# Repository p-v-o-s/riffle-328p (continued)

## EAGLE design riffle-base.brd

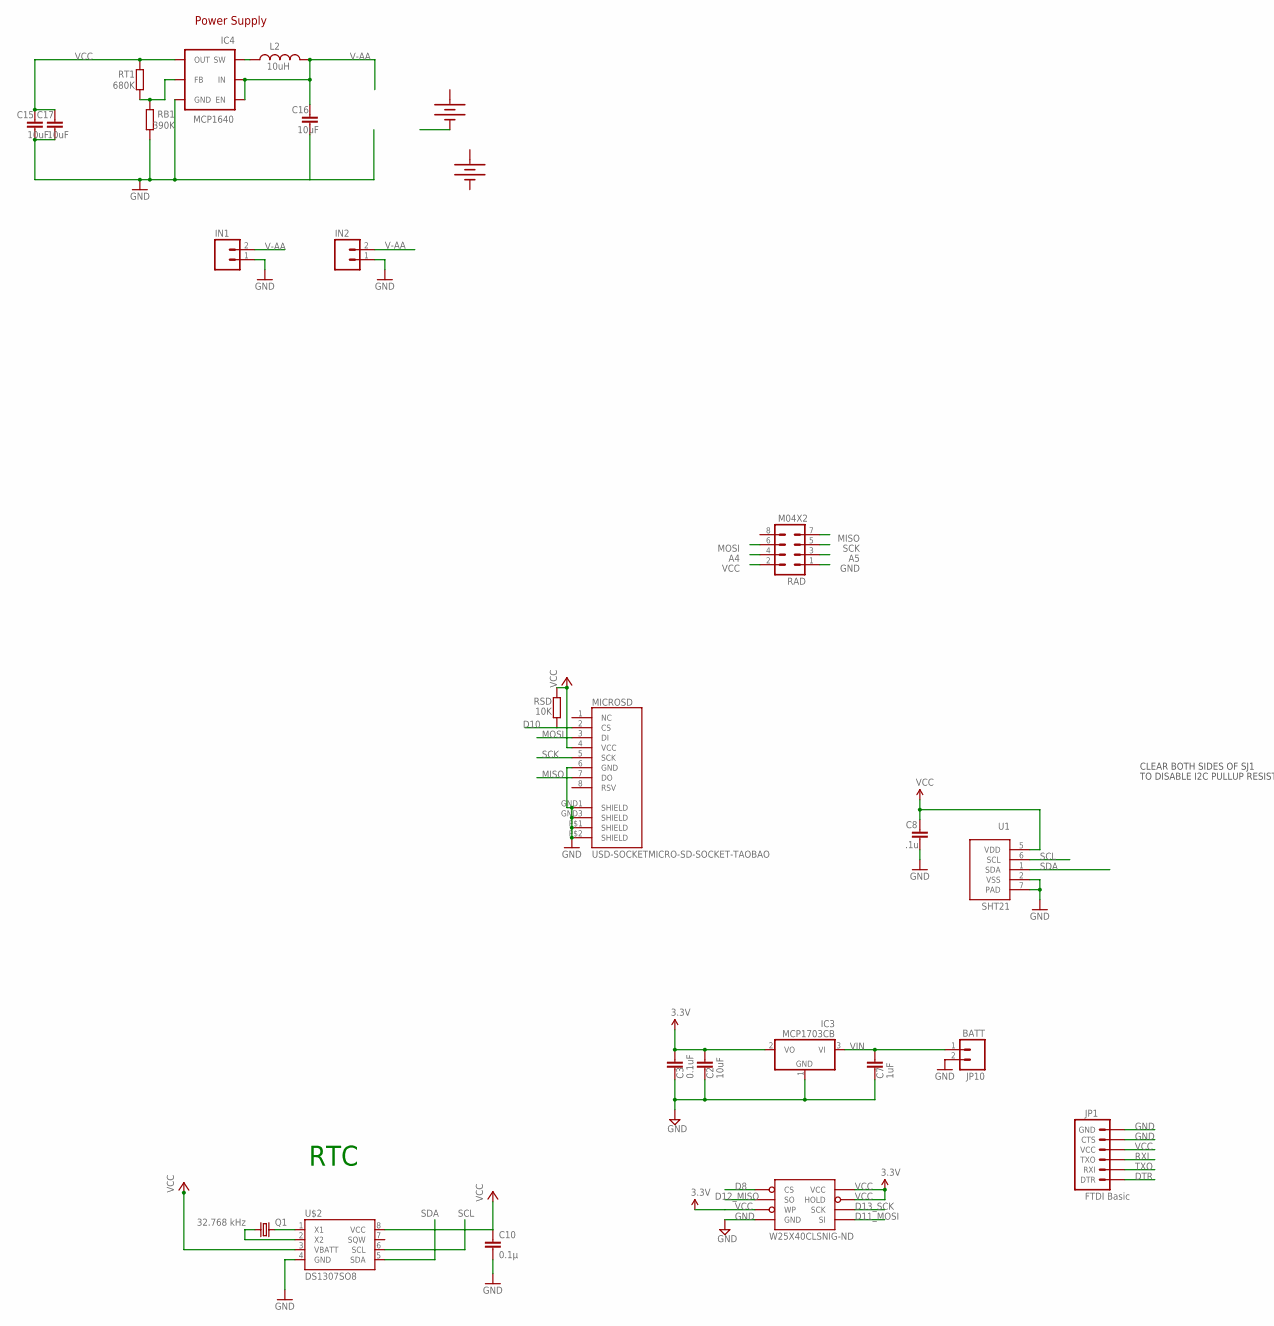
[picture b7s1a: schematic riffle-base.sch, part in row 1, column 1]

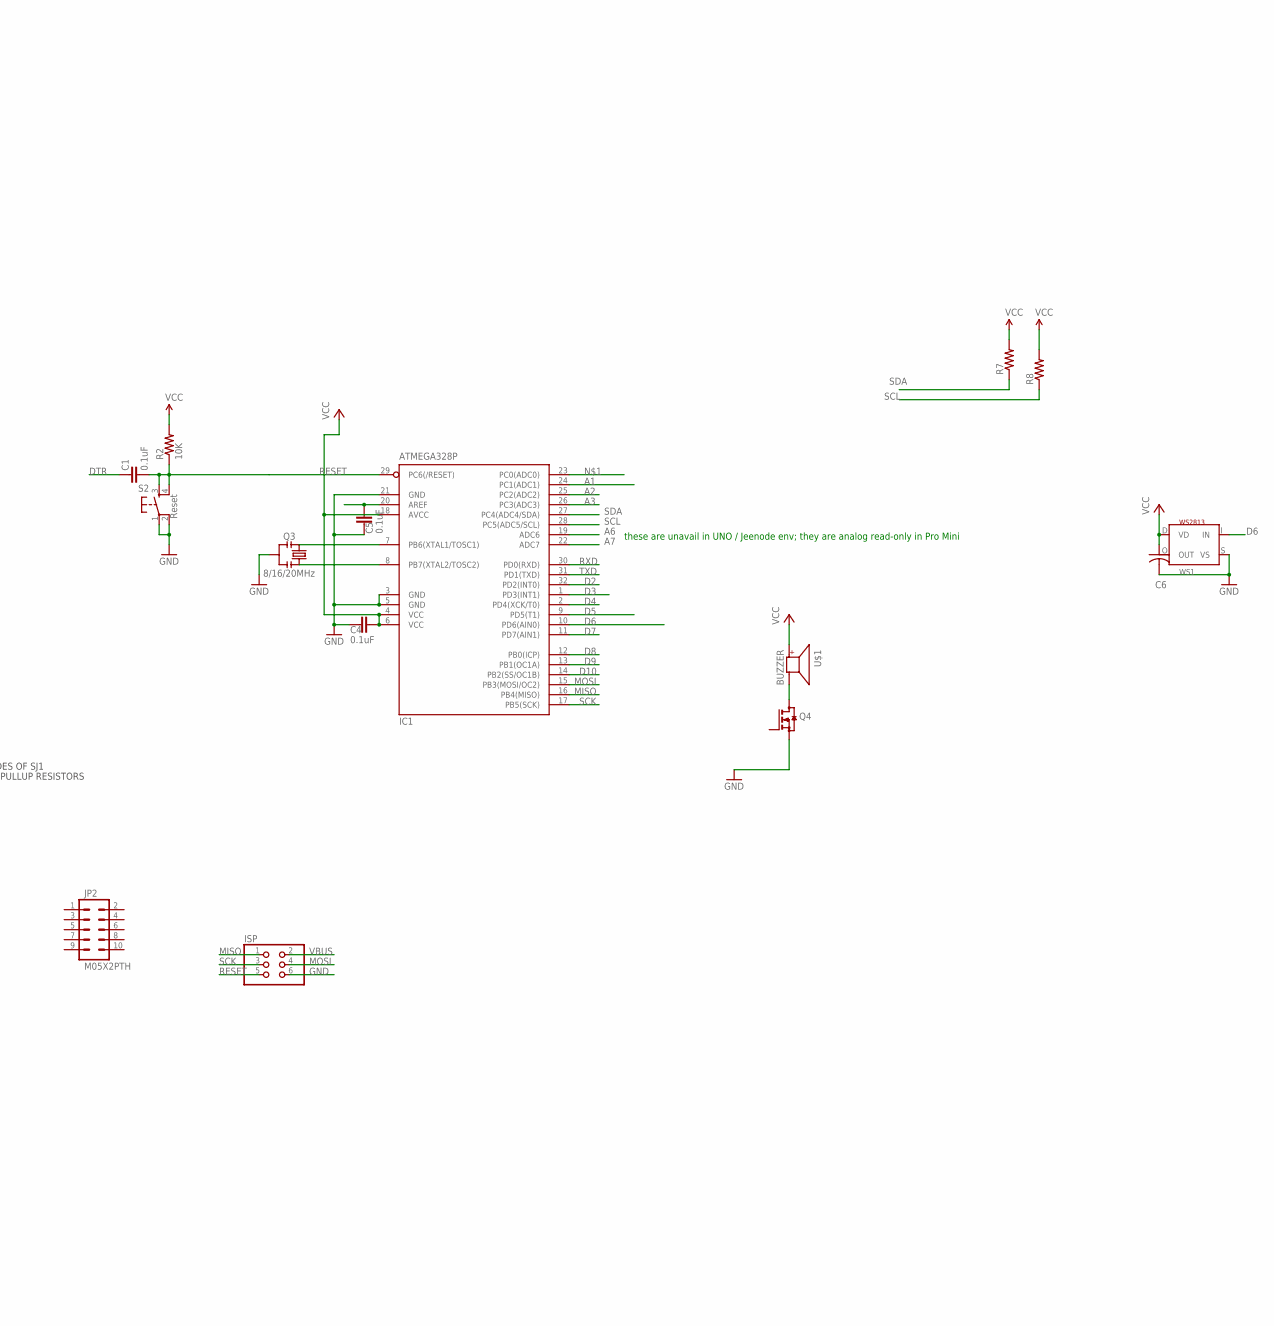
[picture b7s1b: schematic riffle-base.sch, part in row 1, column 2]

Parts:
AA1, AA2: BATTERYAA; BATTERY-AA
C1: 0.1uF; 0402-CAP
C2, C15, C16, C17: 10uF; C0805
C3, C4, C5: 0.1uF; C0805
C6: C-USC0805K; C0805K
C7: 1uF; C0805
C8: .1u; C0805
C10: 0.1µ; CAP-PTH-SMALL
IC1: ATMEGA328P; TQFP32-08
IC3: MCP1703CB; SOT23
IC4: MCP1640; TSOT23-6
IN1: M02PTH; 1X02
IN2: M02-JST-2MM-SMT; JST-2-SMD
ISP: PINHD-2X3; 2X03
JP1: FTDI Basic; 1X06
JP2: M05X2PTH; AVR_ICSP
JP10: BATT; 1X02_LOCK_LONGPADS
L2: 10uH; INDUCTOR_D30
MICROSD: USD-SOCKETMICRO-SD-SOCKET-TAOBAO; MICRO-SD-SOCKET-TAOBAO
Q1: 32.768 kHz; TC26H
Q3: 8/16/20MHz; RESONATOR-SMD
Q4: BSS123; SOT23
R2: 10K; 0402-RES
R7, R8: RESISTOR0402-RES; 0402-RES
RAD: M04X2; 2X4
RB1: 390K; R0805
RSD: 10K; R0805
RT1: 680K; R0805
S2: Reset; TACTILE_SWITCH_SMD
U1: SHT21; SEN-SENSIRION-SHT2X
U$1: BUZZER; SMT-8585-BUZZER
U$2: DS1307SO8; SO08
W25X40CLSNIG-ND: AT25F512BWIDE_5.3MM; SO08WIDE
WS1: WS2813; RGBLED5050_4

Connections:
+: AA1.PWR@1 (+), AA2.PWR@1 (+)
-: AA1.GND@1 (-)
A1: IC1.24 (PC1(ADC1))
A2: IC1.25 (PC2(ADC2))
A3: IC1.26 (PC3(ADC3))
A4: RAD.4
A5: RAD.3
A6: IC1.19 (ADC6)
A7: IC1.22 (ADC7)
AREF1: C5.2, IC1.20 (AREF)
D2: IC1.32 (PD2(INT0))
D3: IC1.1 (PD3(INT1))
D4: IC1.2 (PD4(XCK/T0))
D5: IC1.9 (PD5(T1))
D6: IC1.10 (PD6(AIN0)), WS1.I (IN)
D7: IC1.11 (PD7(AIN1))
D8: IC1.12 (PB0(ICP)), W25X40CLSNIG-ND.1 (CS)
D9: IC1.13 (PB1(OC1A))
D10: IC1.14 (PB2(SS/OC1B)), MICROSD.2 (CS), RSD.1
D11_MOSI: W25X40CLSNIG-ND.5 (SI)
D12_MISO: W25X40CLSNIG-ND.2 (SO)
D13_SCK: W25X40CLSNIG-ND.6 (SCK)
DTR: C1.2, JP1.1 (DTR)
GND: C2.1, C3.1, C4.1, C5.1, C6.2, C7.1, C8.2, C10.2, C15.2, C16.2, C17.2, IC1.3 (GND), IC1.5 (GND), IC1.21 (GND), IC3.1 (GND), IC4.2 (GND), IN1.1, IN2.1, ISP.6, JP1.5 (CTS), JP1.6 (GND), JP10.2, MICROSD.6 (GND), MICROSD.GND1 (SHIELD), MICROSD.GND3 (SHIELD), MICROSD.P$1 (SHIELD), MICROSD.P$2 (SHIELD), Q3.2, Q4.2 (S), RAD.1, RB1.1, S2.1, S2.2, U1.2 (VSS), U1.7 (PAD), U$2.4 (GND), W25X40CLSNIG-ND.4 (GND), WS1.S (VS)
GND1: AA2.GND@1 (-)
MISO: IC1.16 (PB4(MISO)), ISP.1, MICROSD.7 (DO), RAD.7
MOSI: IC1.15 (PB3(MOSI/OC2)), ISP.4, MICROSD.3 (DI), RAD.6
unnamed: IC1.7 (PB6(XTAL1/TOSC1)), Q3.3
unnamed: IC1.8 (PB7(XTAL2/TOSC2)), Q3.1
unnamed: Q4.3 (D), U$1.-
unnamed: Q1.2, U$2.1 (X1)
unnamed: Q1.1, U$2.2 (X2)
unnamed: IC4.1 (SW), L2.P$2 (2)
unnamed: IC4.4 (FB), RB1.2, RT1.1
RESET: ISP.5
RESET1: C1.1, R2.1, S2.3, S2.4
RXD: IC1.30 (PD0(RXD))
RXI: JP1.3 (TXO)
SCK: IC1.17 (PB5(SCK)), ISP.3, MICROSD.5 (SCK), RAD.5
SCL: IC1.28 (PC5(ADC5/SCL)), R8.1, U1.6 (SCL), U$2.6 (SCL)
SDA: IC1.27 (PC4(ADC4/SDA)), R7.1, U1.1 (SDA), U$2.5 (SDA)
TXD: IC1.31 (PD1(TXD))
TXO: JP1.2 (RXI)
V-AA: C16.1, IC4.3 (EN), IC4.6 (IN), IN1.2, IN2.2, L2.P$1 (1)
VBUS: ISP.2
VCC: C2.2, C3.2, C4.2, C6.1, C8.1, C10.1, C15.1, C17.1, IC1.4 (VCC), IC1.6 (VCC), IC1.18 (AVCC), IC3.2 (VO), IC4.5 (OUT), JP1.4 (VCC), MICROSD.4 (VCC), R2.2, R7.2, R8.2, RAD.2, RSD.2, RT1.2, U1.5 (VDD), U$1.+, U$2.3 (VBATT), U$2.8 (VCC), W25X40CLSNIG-ND.3 (WP), W25X40CLSNIG-ND.7 (HOLD), W25X40CLSNIG-ND.8 (VCC), WS1.D (VD)
VIN: C7.2, IC3.3 (VI), JP10.1

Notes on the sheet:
RTC
CLEAR BOTH SIDES OF SJ1
TO DISABLE I2C PULLUP RESISTORS
Power Supply
these are unavail in UNO / Jeenode env; they are analog read-only in Pro Mini

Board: 2 copper layers, 41 parts (1 on the bottom side), 23 nets, no tracks yet.

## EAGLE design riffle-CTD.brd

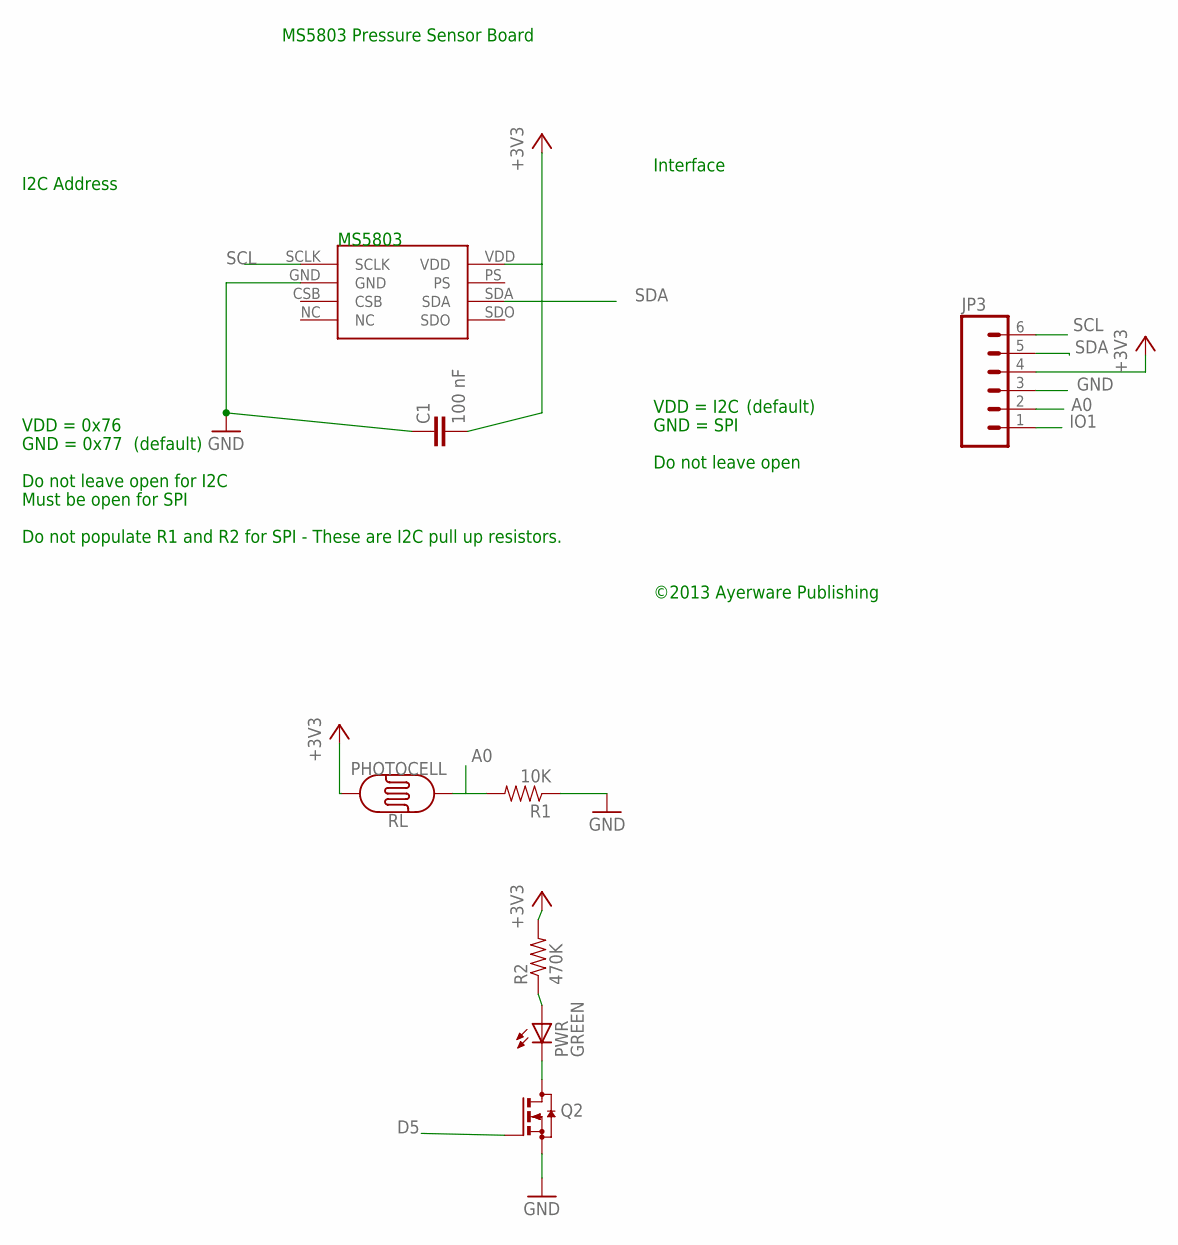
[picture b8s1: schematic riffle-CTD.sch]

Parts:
C1: 100 nF; 0402-CAP
JP3: M06SIP; 1X06
MS5803: MS5803-14BA
PWR: GREEN; CHIPLED_0805
Q2: BSS123; SOT23
R1: 10K; 0402-RES
R2: 470K; 0402-RES
RL: PHOTOCELL

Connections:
+3V3: C1.1, JP3.4, MS5803.VDD, R2.2, RL.2
A0: JP3.2, R1.2, RL.1
D5: Q2.1 (G)
GND: C1.2, JP3.3, MS5803.GND, Q2.2 (S), R1.1
IO1: JP3.1
unnamed: PWR.C, Q2.3 (D)
unnamed: PWR.A, R2.1
SCL: JP3.6, MS5803.SCLK
SDA: JP3.5, MS5803.SDA

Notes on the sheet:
I2C Address
GND = 0x77
Interface
VDD = I2C
VDD = 0x76
GND = SPI
Do not leave open for I2C
Do not leave open
Must be open for SPI
MS5803
©2013 Ayerware Publishing
MS5803 Pressure Sensor Board
Do not populate R1 and R2 for SPI - These are I2C pull up resistors.
(default)

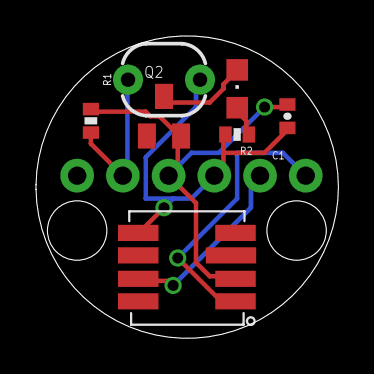
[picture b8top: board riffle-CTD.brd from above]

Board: 2 copper layers, 16.8 x 16.8 mm, 8 parts (0 on the bottom side), 7 nets.
